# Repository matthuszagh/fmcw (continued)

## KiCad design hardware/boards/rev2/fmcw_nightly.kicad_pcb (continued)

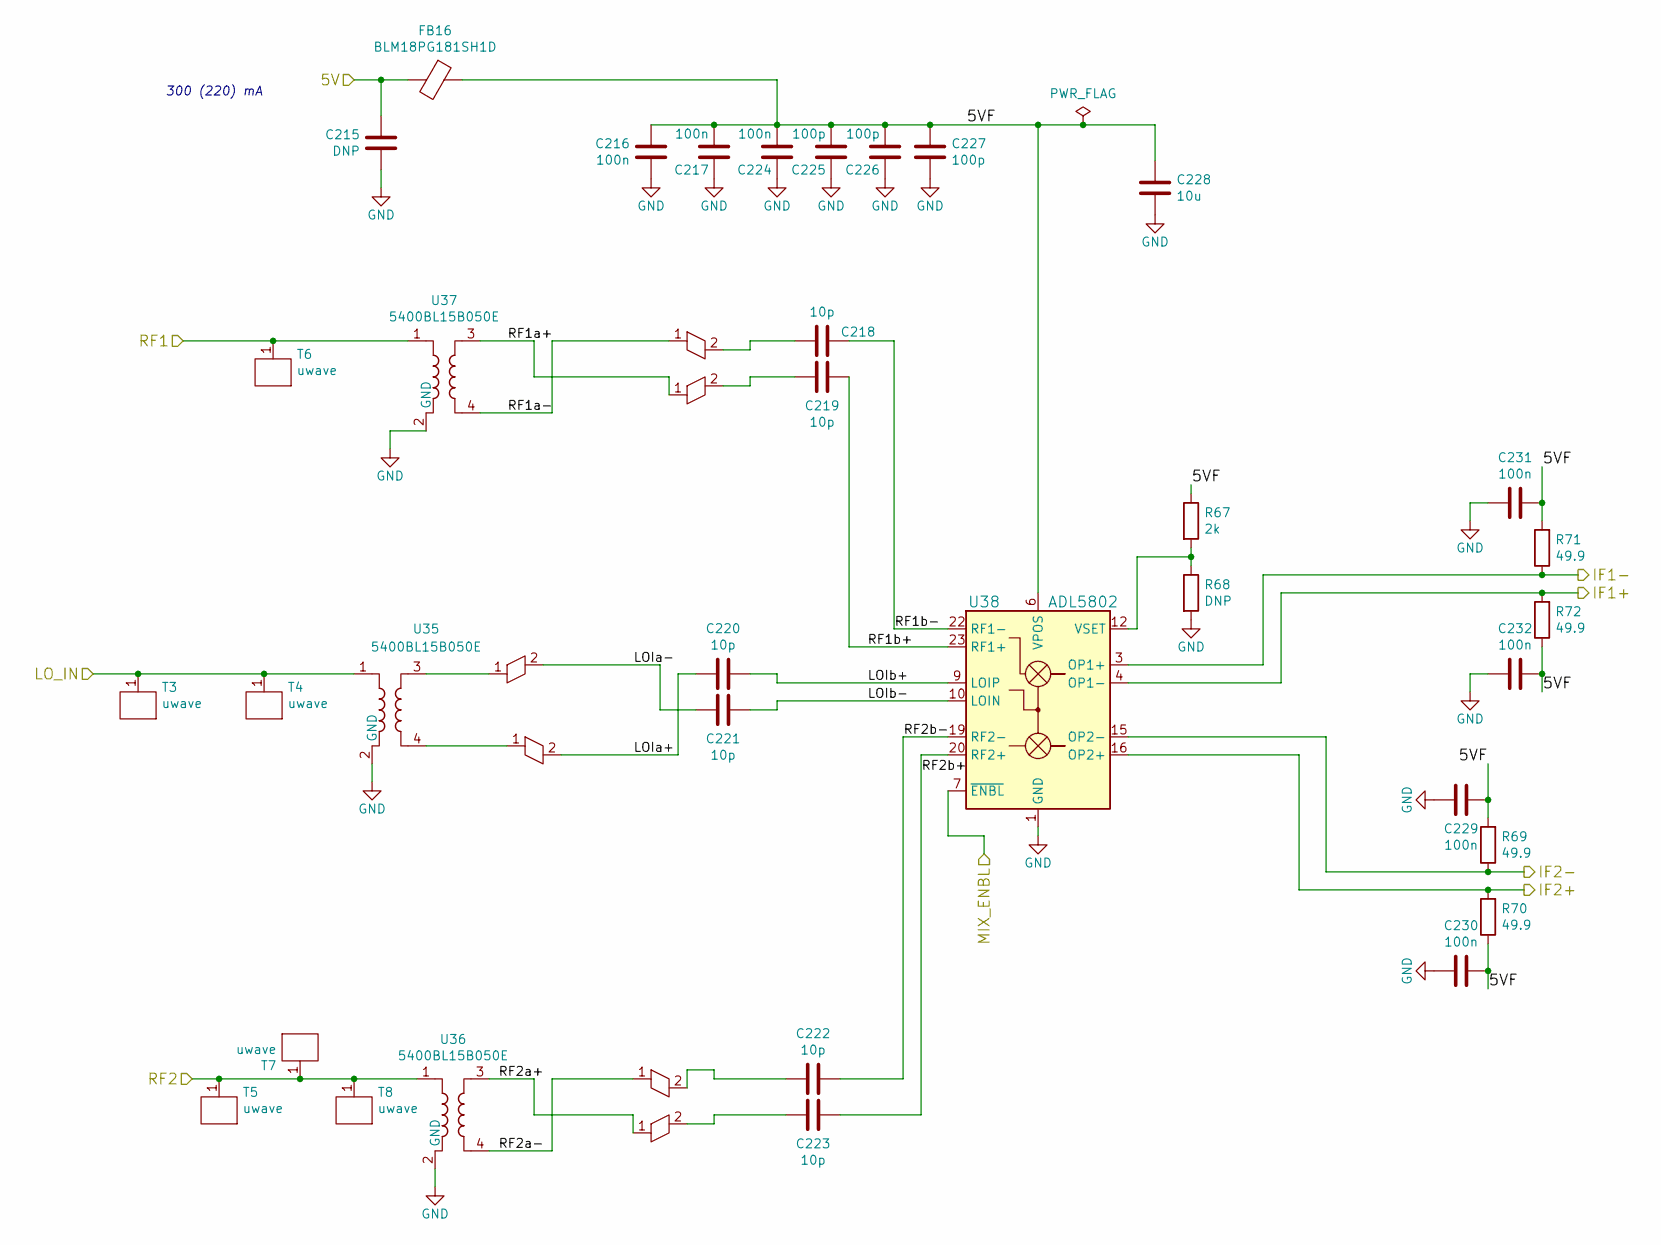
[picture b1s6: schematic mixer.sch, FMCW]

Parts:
C215: DNP; C_0805_2012Metric
C216, C217, C224, C229, C230, C231, C232: 100n; C_0402_1005Metric
C218, C219, C220, C221, C222, C223: 10p; RF_C_0201_0603Metric
C225, C226, C227: 100p; C_0402_1005Metric
C228: 10u; C_0805_2012Metric
FB16: BLM18PG181SH1D; L_0603_1608Metric
JP2, JP4, JP17: balun_exit_inv
JP3, JP5, JP18: balun_exit
R67: 2k; R_0402_1005Metric
R68: DNP; R_0402_1005Metric
R69, R70, R71, R72: 49.9; R_0402_1005Metric
T3, T4, T5, T6, T7, T8: uwave; uwm_0.38_0.17_90
U35, U36, U37: 5400BL15B050E; Balun_Johanson_5400BL15B050E
U38: ADL5802; LFCSP-24-1EP_4x4mm_P0.5mm_EP2.5x2.5mm_ThermalVias

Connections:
/5VMIX: C215.2, FB16.2; also elsewhere on the board
/IF1+: R72.2, U38.4 (OP1-); also elsewhere on the board
/IF1-: R71.1, U38.3 (OP1+); also elsewhere on the board
/IF2+: R70.2, U38.16 (OP2+); also elsewhere on the board
/IF2-: R69.1, U38.15 (OP2-); also elsewhere on the board
/LO: T3.1, T4.1, U35.1; also elsewhere on the board
/MIX_ENBL: U38.7 (~ENBL); also elsewhere on the board
/RF1: T6.1, U37.1; also elsewhere on the board
/RF2: T5.1, T7.1, T8.1, U36.1; also elsewhere on the board
/mixer/5VF: C216.2, C217.2, C224.2, C225.2, C226.2, C227.2, C228.2, C229.2, C230.2, C231.2, C232.2, FB16.1, R67.1, R69.2, R70.1, R71.2, R72.1, U38.6 (VPOS), U38.13 (VPOS), U38.24 (VPOS)
/mixer/LOIa+: C220.2, JP18.2
/mixer/LOIa-: C221.2, JP17.2
/mixer/LOIb+: C220.1, U38.9 (LOIP)
/mixer/LOIb-: C221.1, U38.10 (LOIN)
/mixer/RF1a+: JP4.1, U37.3
/mixer/RF1a-: JP5.1, U37.4
/mixer/RF1b+: C219.1, U38.23 (RF1+)
/mixer/RF1b-: C218.1, U38.22 (RF1-)
/mixer/RF2a+: JP2.1, U36.3
/mixer/RF2a-: JP3.1, U36.4
/mixer/RF2b+: C223.1, U38.20 (RF2+)
/mixer/RF2b-: C222.1, U38.19 (RF2-)
GND: C215.1, C216.1, C217.1, C224.1, C225.1, C226.1, C227.1, C228.1, C229.1, C230.1, C231.1, C232.1, R68.2, U35.2 (GND), U35.5 (GND), U36.2 (GND), U36.5 (GND), U37.2 (GND), U37.5 (GND), U38.1 (GND), U38.2 (GND), U38.5 (GND), U38.8 (GND), U38.11 (GND), U38.14 (GND), U38.17 (GND), U38.18 (GND), U38.21 (GND), U38.25 (GND); also elsewhere on the board
unnamed: C218.2, JP5.2
unnamed: C219.2, JP4.2
unnamed: C222.2, JP3.2
unnamed: C223.2, JP2.2
unnamed: JP17.1, U35.3
unnamed: JP18.1, U35.4
unnamed: R67.2, R68.1, U38.12 (VSET)

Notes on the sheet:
300 (220) mA

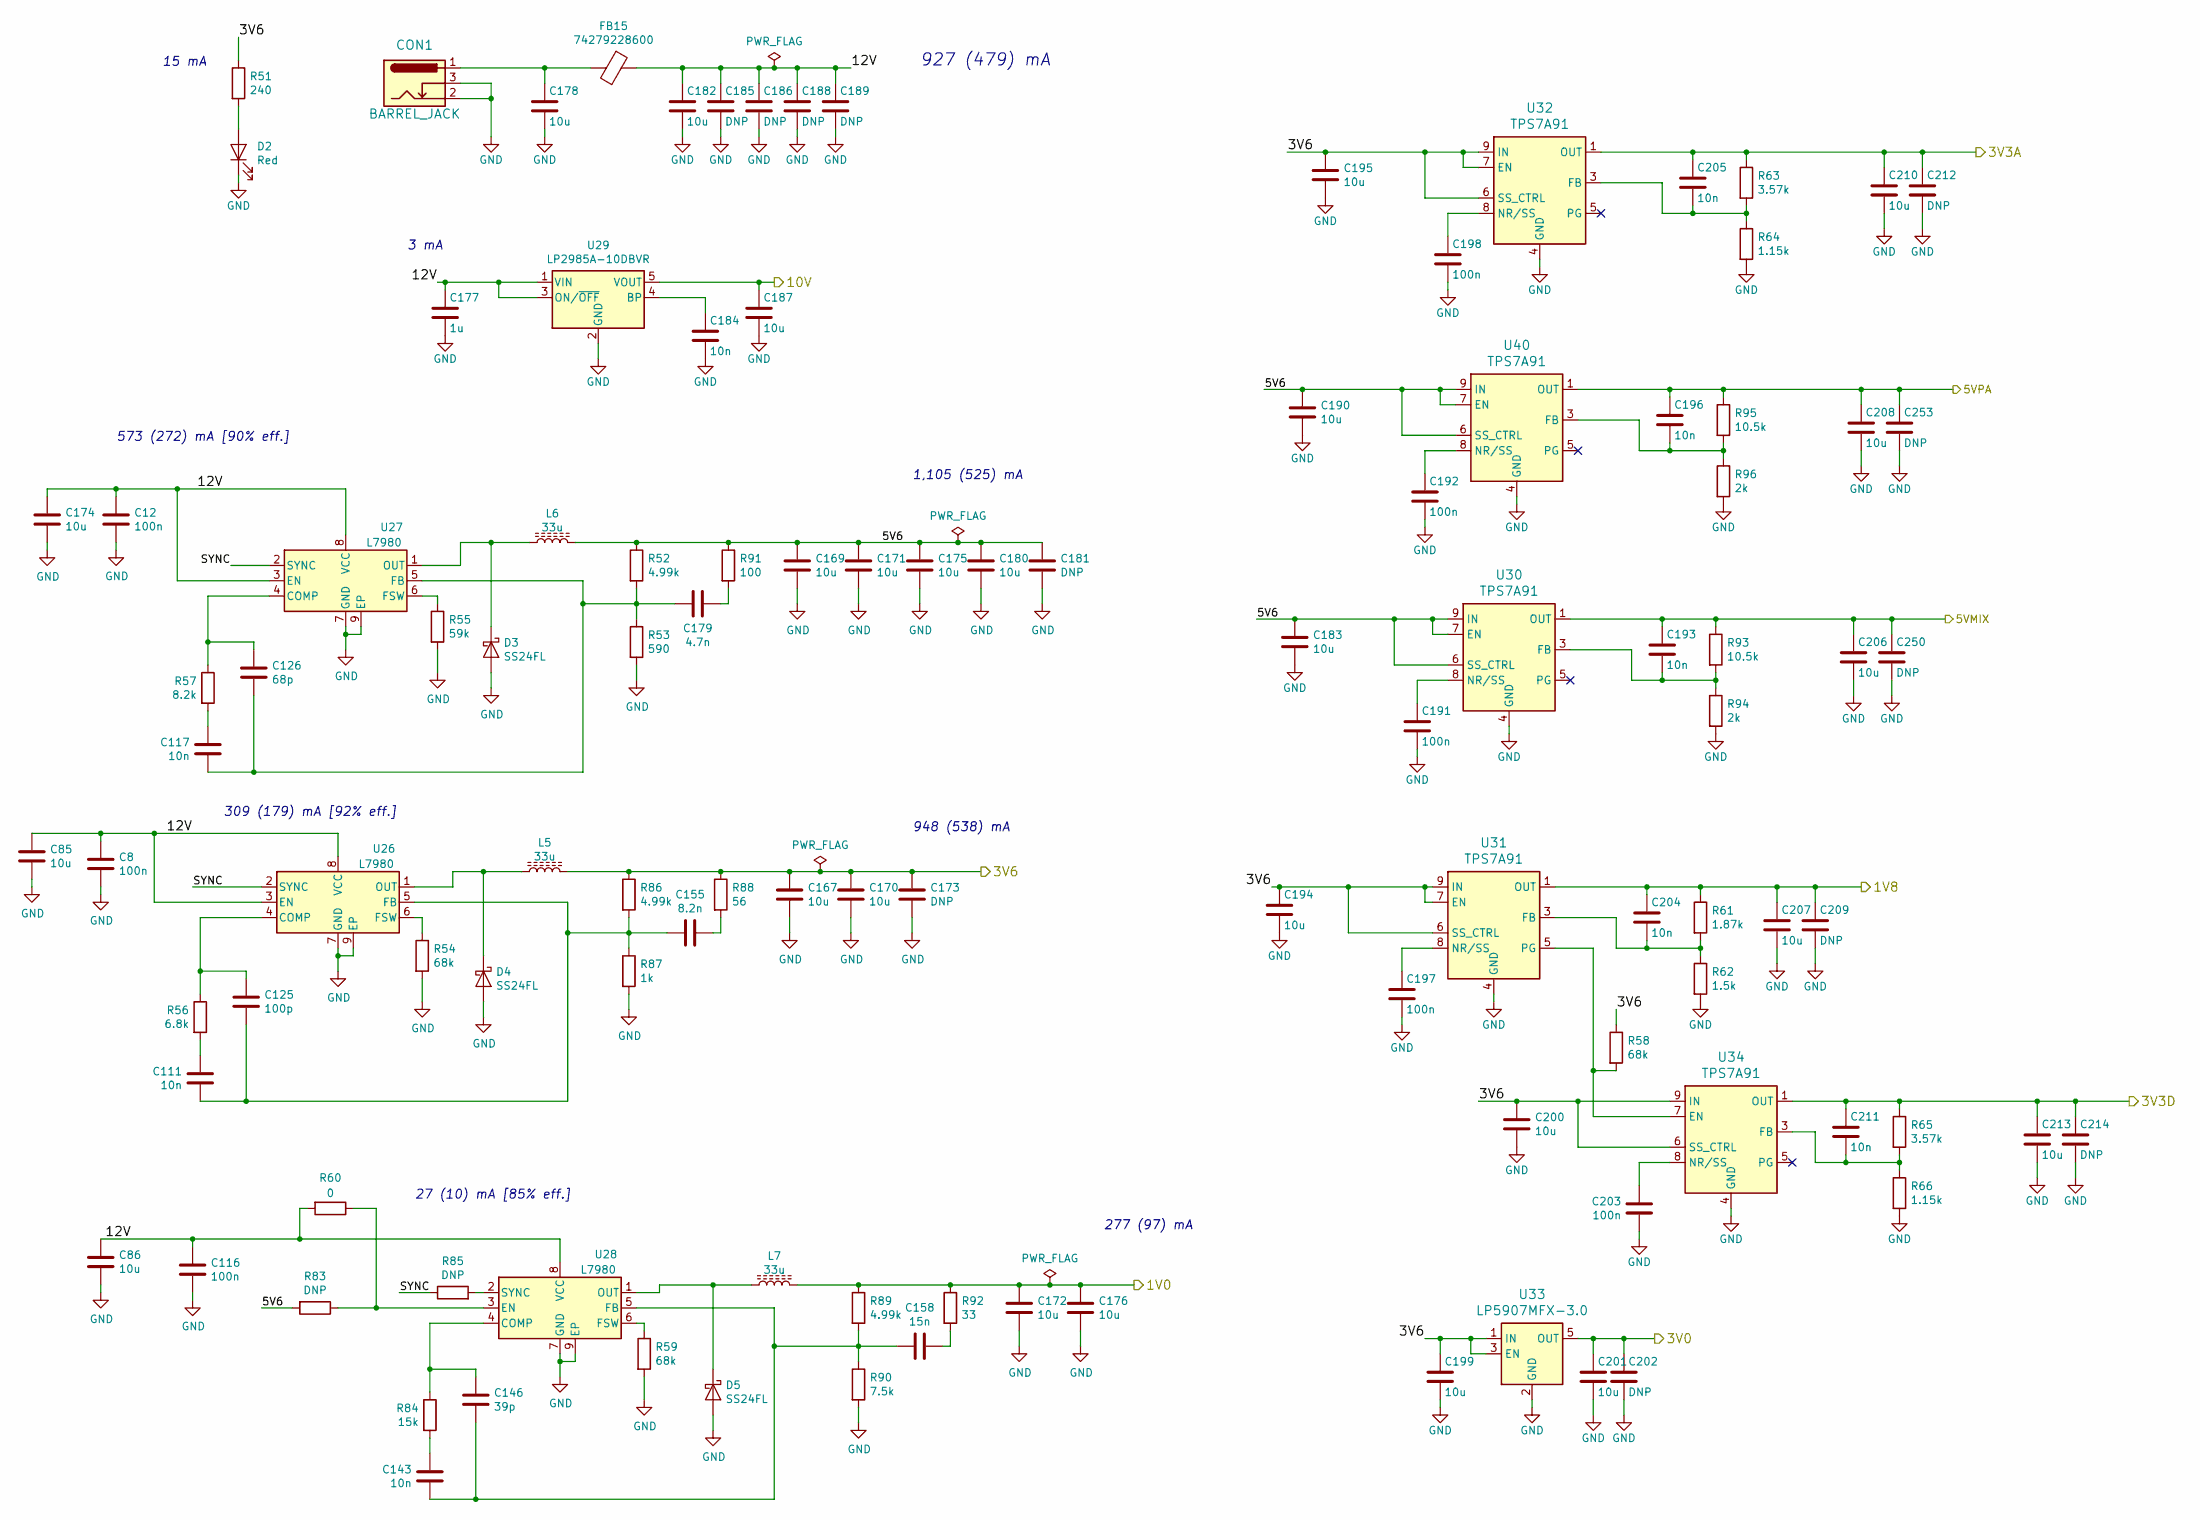
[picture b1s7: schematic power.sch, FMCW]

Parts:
C8, C12, C116, C191, C192, C197, C198, C203: 100n; C_0402_1005Metric
C85, C86, C167, C169, C170, C171, C172, C174, C175, C176, C178, C180, C182, C183, C187, C190, C194, C195, C199, C200, C201, C206, C207, C208, C210, C213: 10u; C_0805_2012Metric
C111, C117, C143, C184, C193, C196, C204, C205, C211: 10n; C_0402_1005Metric
C125: 100p; C_0402_1005Metric
C126: 68p; C_0402_1005Metric
C146: 39p; C_0402_1005Metric
C155: 8.2n; C_0402_1005Metric
C158: 15n; C_0402_1005Metric
C173, C181, C185, C186, C188, C189, C202, C209, C212, C214, C250, C253: DNP; C_0805_2012Metric
C177: 1u; C_0603_1608Metric
C179: 4.7n; C_0402_1005Metric
CON1: BARREL_JACK; BarrelJack_Wuerth_6941xx301002
D2: Red; LED_0603_1608Metric
D3, D4, D5: SS24FL; D_SOD-123F
FB15: 74279228600; L_0603_1608Metric
L5, L6: 33u; L_Wuerth_HCI-1365
L7: 33u; SRR6040A
R51: 240; R_0402_1005Metric
R52, R86, R89: 4.99k; R_0402_1005Metric
R53: 590; R_0402_1005Metric
R54, R58, R59: 68k; R_0402_1005Metric
R55: 59k; R_0402_1005Metric
R56: 6.8k; R_0402_1005Metric
R57: 8.2k; R_0402_1005Metric
R60: 0; R_0402_1005Metric
R61: 1.87k; R_0402_1005Metric
R62: 1.5k; R_0402_1005Metric
R63, R65: 3.57k; R_0402_1005Metric
R64, R66: 1.15k; R_0402_1005Metric
R83, R85: DNP; R_0402_1005Metric
R84: 15k; R_0402_1005Metric
R87: 1k; R_0402_1005Metric
R88: 56; R_0402_1005Metric
R90: 7.5k; R_0402_1005Metric
R91: 100; R_0402_1005Metric
R92: 33; R_0402_1005Metric
R93, R95: 10.5k; R_0402_1005Metric
R94, R96: 2k; R_0402_1005Metric
U26, U27, U28: L7980; HSOP-8-1EP_3.9x4.9mm_P1.27mm_EP2.3x2.3mm_ThermalVias
U29: LP2985A-10DBVR; SOT-23-5
U30, U31, U32, U34, U40: TPS7A91; Texas_S-PDSO-N10_EP1.2x2mm
U33: LP5907MFX-3.0; SOT-23-5

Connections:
/1V0: C172.1, C176.1, L7.2, R89.1, R92.1; also elsewhere on the board
/1V8: C204.1, C207.1, C209.1, R61.1, U31.1 (OUT), U31.2 (OUT); also elsewhere on the board
/3V0: C201.1, C202.1, U33.5 (OUT); also elsewhere on the board
/3V3A: C205.1, C210.1, C212.1, R63.1, U32.1 (OUT), U32.2 (OUT); also elsewhere on the board
/3V6: C167.1, C170.1, C173.1, C194.1, C195.1, C199.1, C200.1, L5.2, R51.1, R58.1, R86.1, R88.1, U31.6 (SS_CTRL), U31.7 (EN), U31.9 (IN), U31.10 (IN), U32.6 (SS_CTRL), U32.7 (EN), U32.9 (IN), U32.10 (IN), U33.1 (IN), U33.3 (EN), U34.6 (SS_CTRL), U34.9 (IN), U34.10 (IN); also elsewhere on the board
/5VMIX: C193.1, C206.1, C250.1, R93.1, U30.1 (OUT), U30.2 (OUT); also elsewhere on the board
/5VPA: C196.1, C208.1, C253.1, R95.1, U40.1 (OUT), U40.2 (OUT); also elsewhere on the board
/10V: C187.1, U29.5 (VOUT); also elsewhere on the board
/power/5V6: C169.1, C171.1, C175.1, C180.1, C181.1, C183.1, C190.1, L6.2, R52.1, R83.2, R91.1, U30.6 (SS_CTRL), U30.7 (EN), U30.9 (IN), U30.10 (IN), U40.6 (SS_CTRL), U40.7 (EN), U40.9 (IN), U40.10 (IN)
/power/12V: C8.1, C12.1, C85.1, C86.1, C116.1, C174.1, C177.1, C182.1, C185.1, C186.1, C188.1, C189.1, FB15.1, R60.2, U26.3 (EN), U26.8 (VCC), U27.3 (EN), U27.8 (VCC), U28.8 (VCC), U29.1 (VIN), U29.3 (ON/~OFF~)
/power/SYNC: R85.1, U26.2 (SYNC), U27.2 (SYNC)
GND: C8.2, C12.2, C85.2, C86.2, C116.2, C167.2, C169.2, C170.2, C171.2, C172.2, C173.2, C174.2, C175.2, C176.2, C177.2, C178.2, C180.2, C181.2, C182.2, C183.2, C184.2, C185.2, C186.2, C187.2, C188.2, C189.2, C190.2, C191.2, C192.2, C194.2, C195.2, C197.2, C198.2, C199.2, C200.2, C201.2, C202.2, C203.2, C206.2, C207.2, C208.2, C209.2, C210.2, C212.2, C213.2, C214.2, C250.2, C253.2, CON1.2, CON1.3, D2.1 (K), D3.2 (A), D4.2 (A), D5.2 (A), R53.2, R54.2, R55.2, R59.2, R62.2, R64.2, R66.2, R87.2, R90.2, R94.2, R96.2, U26.7 (GND), U26.9 (EP), U27.7 (GND), U27.9 (EP), U28.7 (GND), U28.9 (EP), U29.2 (GND), U30.4 (GND), U30.11 (GND), U31.4 (GND), U31.11 (GND), U32.4 (GND), U32.11 (GND), U33.2 (GND), U34.4 (GND), U34.11 (GND), U40.4 (GND), U40.11 (GND); also elsewhere on the board
unnamed: C111.1, R56.2
unnamed: C111.2, C125.2, C155.2, R86.2, R87.1, U26.5 (FB)
unnamed: C117.1, R57.2
unnamed: C117.2, C126.2, C179.2, R52.2, R53.1, U27.5 (FB)
unnamed: C125.1, R56.1, U26.4 (COMP)
unnamed: C126.1, R57.1, U27.4 (COMP)
unnamed: C143.1, R84.2
unnamed: C143.2, C146.2, C158.2, R89.2, R90.1, U28.5 (FB)
unnamed: C146.1, R84.1, U28.4 (COMP)
unnamed: C155.1, R88.2
unnamed: C158.1, R92.2
unnamed: C178.1, CON1.1, FB15.2
unnamed: C179.1, R91.2
unnamed: C184.1, U29.4 (BP)
unnamed: C191.1, U30.8 (NR/SS)
unnamed: C192.1, U40.8 (NR/SS)
unnamed: C193.2, R93.2, R94.1, U30.3 (FB)
unnamed: C196.2, R95.2, R96.1, U40.3 (FB)
unnamed: C197.1, U31.8 (NR/SS)
unnamed: C198.1, U32.8 (NR/SS)
unnamed: C203.1, U34.8 (NR/SS)
unnamed: C204.2, R61.2, R62.1, U31.3 (FB)
unnamed: C205.2, R63.2, R64.1, U32.3 (FB)
unnamed: C211.2, R65.2, R66.1, U34.3 (FB)
unnamed: D2.2 (A), R51.2
unnamed: D3.1 (K), L6.1, U27.1 (OUT)
unnamed: D4.1 (K), L5.1, U26.1 (OUT)
unnamed: D5.1 (K), L7.1, U28.1 (OUT)
unnamed: R54.1, U26.6 (FSW)
unnamed: R55.1, U27.6 (FSW)
unnamed: R58.2, U31.5 (PG), U34.7 (EN)
unnamed: R59.1, U28.6 (FSW)
unnamed: R60.1, R83.1, U28.3 (EN)
unnamed: R85.2, U28.2 (SYNC)

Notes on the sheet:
573 (272) mA [90% eff.]
15 mA
309 (179) mA [92% eff.]
3 mA
27 (10) mA [85% eff.]
1,105 (525) mA
948 (538) mA
927 (479) mA
277 (97) mA

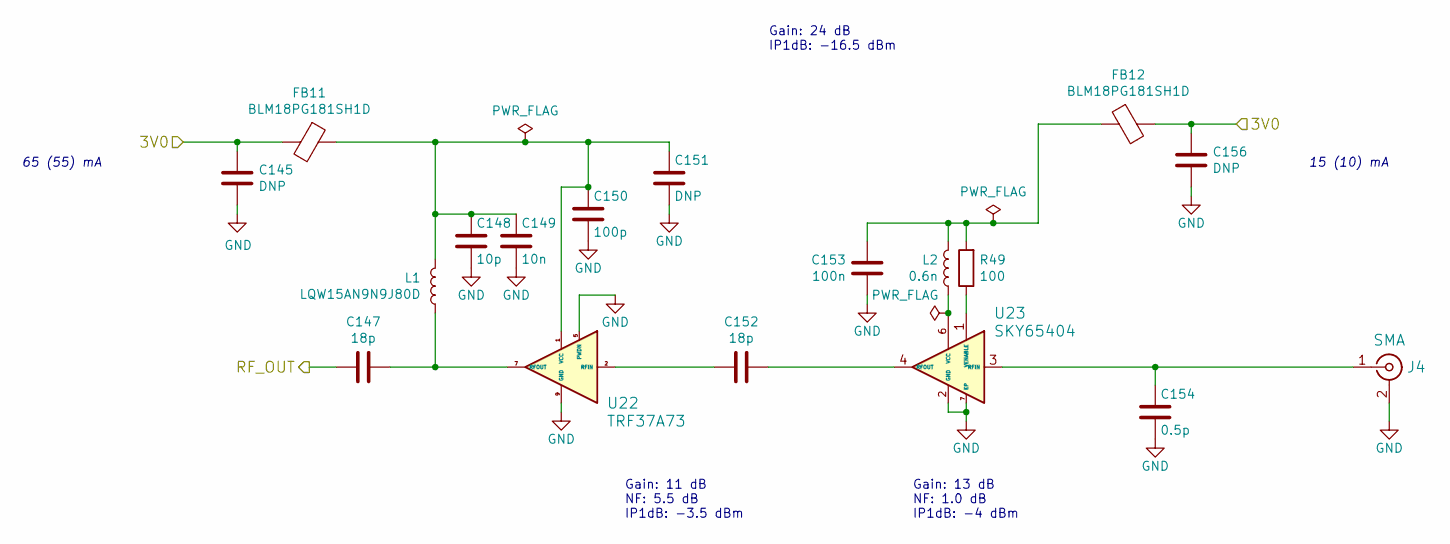
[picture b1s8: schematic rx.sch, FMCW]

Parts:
C145, C156: DNP; C_0805_2012Metric
C147, C152: 18p; RF_C_0201_0603Metric
C148: 10p; C_0402_1005Metric
C149: 10n; C_0402_1005Metric
C150: 100p; C_0402_1005Metric
C153: 100n; C_0402_1005Metric
C154: 0.5p; RF_C_0201_0603Metric
C163: DNP; C_0603_1608Metric
FB13, FB14: BLM18PG181SH1D; L_0603_1608Metric
J4: SMA; SMA_901-10512
L1: LQW15AN9N9J80D; RF_Bypass_C_0402_1005Metric
L2: 0.6n; L_0402_1005Metric
R49: 100; R_0402_1005Metric
U22: TRF37A73; WSON-8-1EP_2x2mm_P0.5mm_EP0.9x1.6mm_ThermalVias
U23: SKY65404; Skyworks_SKY65404-31

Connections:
/3V0: C145.1, C156.1, FB13.2, FB14.2; also elsewhere on the board
/RF1: C147.2; also elsewhere on the board
GND: C145.2, C148.2, C149.2, C150.2, C153.2, C154.2, C156.2, C163.2, J4.2 (Ext), U22.5 (PWDN), U22.9 (GND), U23.2 (GND), U23.5 (GND), U23.7 (EP); also elsewhere on the board
unnamed: C147.1, L1.1, U22.7 (RFOUT)
unnamed: C152.1, U23.4 (RFOUT)
unnamed: C152.2, U22.2 (RFIN)
unnamed: C154.1, J4.1 (In), U23.3 (RFIN)
unnamed: L2.1, U23.6 (VCC)
unnamed: R49.1, U23.1 (VENABLE)

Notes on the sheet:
65 (55) mA
Gain: 11 dB NF: 5.5 dB IP1dB: -3.5 dBm
Gain: 24 dB IP1dB: -16.5 dBm
Gain: 13 dB NF: 1.0 dB IP1dB: -4 dBm
15 (10) mA

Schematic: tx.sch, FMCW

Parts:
C4, C118: 10u; C_0805_2012Metric
C6, C124: 220p; C_0402_1005Metric
C102, C104, C105, C108, C115, C121, C127, C131, C135: 100n; C_0402_1005Metric
C103, C106, C107, C109: 10p; C_0402_1005Metric
C110: 2.2n; C_0402_1005Metric
C112, C251, C252: 10p; RF_C_0201_0603Metric
C113: DNP; C_0805_2012Metric
C114: 51p; C_0402_1005Metric
C119: 10n; C_0402_1005Metric
C120: 68p; C_0402_1005Metric
C267: 0.3p; RF_C_0201_0603Metric
FB6, FB7: BLM18PG181SH1D; L_0603_1608Metric
FB8: CIC21P101NE; L_0805_2012Metric
J3: SMA; SMA_901-10512
L12: 4.7n; L_0402_1005Metric
Q2: RE1C002UN; SOT-416
R37: 5.49k; R_0402_1005Metric
R38, R44: DNP; R_0402_1005Metric
R39: 3.09k; R_0402_1005Metric
R40, R41, R42: 4.7k; R_0402_1005Metric
R43: 47k; R_0402_1005Metric
R45: 1.5k; R_0402_1005Metric
R46: 10k; R_0402_1005Metric
R47: 100; R_0603b
R48: 49.9; R_0402_1005Metric
R97: 1.3k; R_0402_1005Metric
R114: 510; R_0402_1005Metric
R115: 3.3; R_0402_1005Metric
T1, T2: uwave; uwm_0.38_0.17_90
U12: ADF4158; LFCSP-24-1EP_4x4mm_P0.5mm_EP2.5x2.5mm_ThermalVias
U13: TLV172DCK; SOT-353_SC-70-5
U14: PAT1220-C-3DB; RF_Attenuator_Susumu_PAT1220
U15: HMC431; QFN-24-1EP_4x4mm_P0.5mm_EP2.8x2.8mm_ThermalVias
U16: PD4859J5050S2HF; Anaren_0805_2012Metric-6
U17: PAT1220-C-5DB; RF_Attenuator_Susumu_PAT1220
U18: SE5004L; Skyworks_SE5004L
U20: PAT1220-C-6DB; RF_Attenuator_Susumu_PAT1220
U21: LMV321; SOT-23-5
Z1: BRANCHLINE-fmcw3-rescue; coupler_20db

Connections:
/3V0: FB7.2; also elsewhere on the board
/3V3A: C102.1, C103.1, C104.1, C105.1, C106.1, C121.2, R43.1, R45.1, U12.6 (AVDD), U12.7 (AVDD), U12.8 (AVDD), U12.18 (SDVDD), U12.19 (DVDD), U21.5 (V+); also elsewhere on the board
/5VPA: C113.1, FB6.2, FB8.2; also elsewhere on the board
/10V: C115.2, U13.5 (V+); also elsewhere on the board
/ADF_CE: U12.13 (CE); also elsewhere on the board
/ADF_CLK: U12.14 (CLK); also elsewhere on the board
/ADF_DATA: U12.15 (DATA); also elsewhere on the board
/ADF_LE: U12.16 (LE); also elsewhere on the board
/ADF_MUXOUT: U12.17 (MUXOUT); also elsewhere on the board
/ADF_REF: U12.9 (REFIN); also elsewhere on the board
/ADF_TXDATA: U12.12 (TXDATA); also elsewhere on the board
/LO: U20.1; also elsewhere on the board
/PA_OFF: Q2.1 (G), R43.2, R44.1; also elsewhere on the board
/tx/5V_PA: C4.2, C6.2, C131.1, C135.2, FB8.1, U18.8 (VCC2), U18.9 (VCC3), U18.18 (VCC3), U18.19 (VCC2), U18.20 (VCC1)
/tx/5V_SYNTH: C108.1, C109.1, FB6.1, U12.22 (VP)
GND: C4.1, C102.2, C103.2, C104.2, C105.2, C106.2, C107.1, C108.2, C109.2, C113.2, C114.2, C115.1, C118.1, C119.1, C120.2, C121.1, C131.2, C135.1, C267.1, J3.2 (Ext), Q2.2 (S), R37.2, R39.1, R40.2, R44.2, R46.2, R48.1, R115.1, U12.1 (CPGND), U12.2 (AGND), U12.3 (AGND), U12.10 (DGND), U12.11 (SDGND), U12.25 (AGND), U13.2 (V-), U14.3, U15.1 (NC), U15.2 (NC), U15.3 (NC), U15.4 (NC), U15.5 (NC), U15.6 (NC), U15.7 (NC), U15.8 (NC), U15.9 (NC), U15.10 (NC), U15.11 (NC), U15.12 (NC), U15.13 (NC), U15.14 (NC), U15.15 (GND), U15.17 (NC), U15.18 (NC), U15.19 (NC), U15.21 (NC), U15.23 (NC), U15.24 (NC), U15.25 (GND), U16.1 (GND), U16.3 (GND), U16.5 (GND), U17.3, U18.1 (GND), U20.3, U21.2 (V-); also elsewhere on the board
unnamed: C6.1, R115.2
unnamed: C107.2, U12.4 (RFINB)
unnamed: C110.1, C114.1, U12.24 (CP), U13.1 (+)
unnamed: C110.2, R38.1, R39.2
unnamed: C112.1, U14.1
unnamed: C112.2, U12.5 (RFINA)
unnamed: C118.2, C119.2, FB7.1, U15.20 (VCC)
unnamed: C120.1, R42.1, U15.22 (VTUNE)
unnamed: C124.1, U18.7 (SP2)
unnamed: C124.2, L12.2
unnamed: C127.1, R114.2
unnamed: C127.2, L12.1, R97.1, U18.5 (VREF), U21.4
unnamed: C251.1, U18.3 (RFIN)
unnamed: C251.2, U17.2
unnamed: C252.1, C267.2, Z1.1
unnamed: C252.2, U18.13 (RFOUT)
unnamed: J3.1 (In), Z1.2
unnamed: Q2.3 (D), R45.2, R46.1, U21.1 (+)
unnamed: R37.1, U12.23 (RSET)
unnamed: R38.2, U12.20 (SW1)
unnamed: R40.1, R41.2, U13.3 (-)
unnamed: R41.1, R42.2, U13.4
unnamed: R47.1, U16.4 (Output1), U17.1
unnamed: R47.2, T1.1, T2.1, U14.2, U16.6 (Output2)
unnamed: R48.2, Z1.4
unnamed: R97.2, U21.3 (-)
unnamed: R114.1, U18.6 (SP1)
unnamed: U15.16 (RFOUT), U16.2 (Input)
unnamed: U20.2, Z1.3

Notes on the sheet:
32 (23) mA
-4 dBm
5 mA
3 mA
27mA
10 mA
+2dBm
-1 dBm
2.85V
800 (300) mA
-6 dBm
26 dBm
6 dBm

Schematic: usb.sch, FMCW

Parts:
C59, C62, C63, C64, C65, C69, C70, C71, C72, C73, C74: 100n; C_0402_1005Metric
C60, C61: 15p; C_0402_1005Metric
C66, C67, C68: 4.7u; C_0603_1608Metric
FB3, FB4: BLM18PG181SH1D; L_0603_1608Metric
J2: USB_B_Micro; USB_Micro-B_Amphenol_10103594-0001LF_Horizontal
R3, R17, R27, R82: 10k; R_0402_1005Metric
R18: 2.2k; R_0402_1005Metric
R19: 12k; R_0402_1005Metric
R20, R21: 0; R_0402_1005Metric
R22: 1k; R_0402_1005Metric
R23, R24, R25: 33; R_0402_1005Metric
R26: 4.7k; R_0402_1005Metric
U8: 93LCxxBxxOT; SOT-23-6
U9: FT2232H; LQFP-64_10x10mm_P0.5mm
Y1: 12MHz; ABM10

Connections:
/fpga/CLKOUT: U9.32 (ACBUS5); also elsewhere on the board
/fpga/FT_D0: U9.16 (ADBUS0); also elsewhere on the board
/fpga/FT_D1: U9.17 (ADBUS1); also elsewhere on the board
/fpga/FT_D2: U9.18 (ADBUS2); also elsewhere on the board
/fpga/FT_D3: U9.19 (ADBUS3); also elsewhere on the board
/fpga/FT_D4: U9.21 (ADBUS4); also elsewhere on the board
/fpga/FT_D5: U9.22 (ADBUS5); also elsewhere on the board
/fpga/FT_D6: U9.23 (ADBUS6); also elsewhere on the board
/fpga/FT_D7: U9.24 (ADBUS7); also elsewhere on the board
/fpga/FT_SUSPEND: U9.36 (~SUSPEND); also elsewhere on the board
/fpga/OE#: U9.33 (ACBUS6); also elsewhere on the board
/fpga/RD#: U9.28 (ACBUS2); also elsewhere on the board
/fpga/RXF#: U9.26 (ACBUS0); also elsewhere on the board
/fpga/SIWUA: U9.30 (ACBUS4); also elsewhere on the board
/fpga/TCK: R23.1; also elsewhere on the board
/fpga/TDI: R25.1; also elsewhere on the board
/fpga/TDO: U9.40 (BDBUS2); also elsewhere on the board
/fpga/TMS: R24.1; also elsewhere on the board
/fpga/TXE#: U9.27 (ACBUS1); also elsewhere on the board
/fpga/WR: U9.29 (ACBUS3); also elsewhere on the board
/fpga/usb/1V8: C62.1, C63.1, C64.1, C67.1, U9.12 (VCORE), U9.37 (VCORE), U9.49 (VREGOUT), U9.64 (VCORE)
/fpga/usb/DO: R17.2, R18.1, U8.1 (DO)
/fpga/usb/EECLK: R3.2, U8.4 (CLK), U9.62 (EECLK)
/fpga/usb/EECS: R82.2, U8.5 (CS), U9.63 (EECS)
/fpga/usb/EEDATA: R18.2, U8.3 (DI), U9.61 (EEDATA)
/fpga/usb/USBD_N: R20.1, U9.7 (DM)
/fpga/usb/USBD_P: R21.1, U9.8 (DP)
/fpga/usb/USBDa_N: J2.2 (D-), R20.2
/fpga/usb/USBDa_P: J2.3 (D+), R21.2
/fpga/usb/USB_5V: J2.1 (VBUS), R26.1
GND: C59.2, C60.2, C61.2, C62.2, C63.2, C64.2, C65.1, C66.2, C67.2, C68.2, C69.2, C70.2, C71.2, C72.2, C73.2, C74.2, J2.5 (GND), J2.6 (Shield), R19.2, R27.2, U8.2 (GND), U9.1 (GND), U9.5 (GND), U9.10 (AGND), U9.11 (GND), U9.13 (TEST), U9.15 (GND), U9.25 (GND), U9.35 (GND), U9.47 (GND), U9.51 (GND); also elsewhere on the board
unnamed: C60.1, U9.2 (OSCI), Y1.1
unnamed: C61.1, U9.3 (OSCO), Y1.3
unnamed: C66.1, C69.1, FB4.2, U9.4 (VPHY)
unnamed: C68.1, C70.1, FB3.1, U9.9 (VPLL)
unnamed: R19.1, U9.6 (REF)
unnamed: R22.1, U9.14 (~RESET)
unnamed: R23.2, U9.38 (BDBUS0)
unnamed: R24.2, U9.41 (BDBUS3)
unnamed: R25.2, U9.39 (BDBUS1)
unnamed: R26.2, R27.1, U9.59 (BCBUS7)

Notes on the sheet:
70 mA
150 mA

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
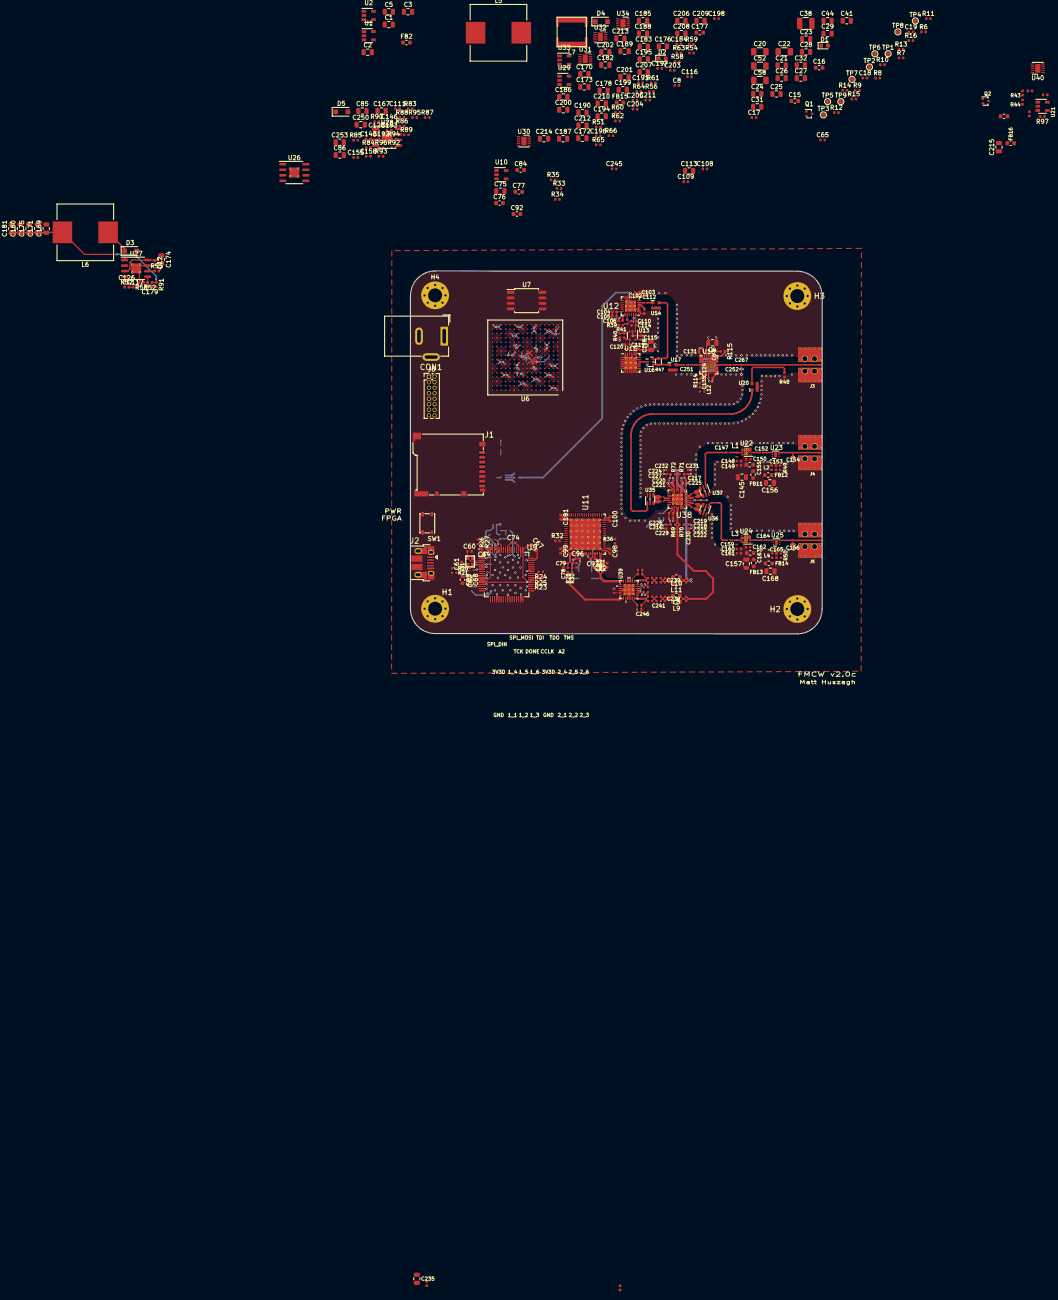
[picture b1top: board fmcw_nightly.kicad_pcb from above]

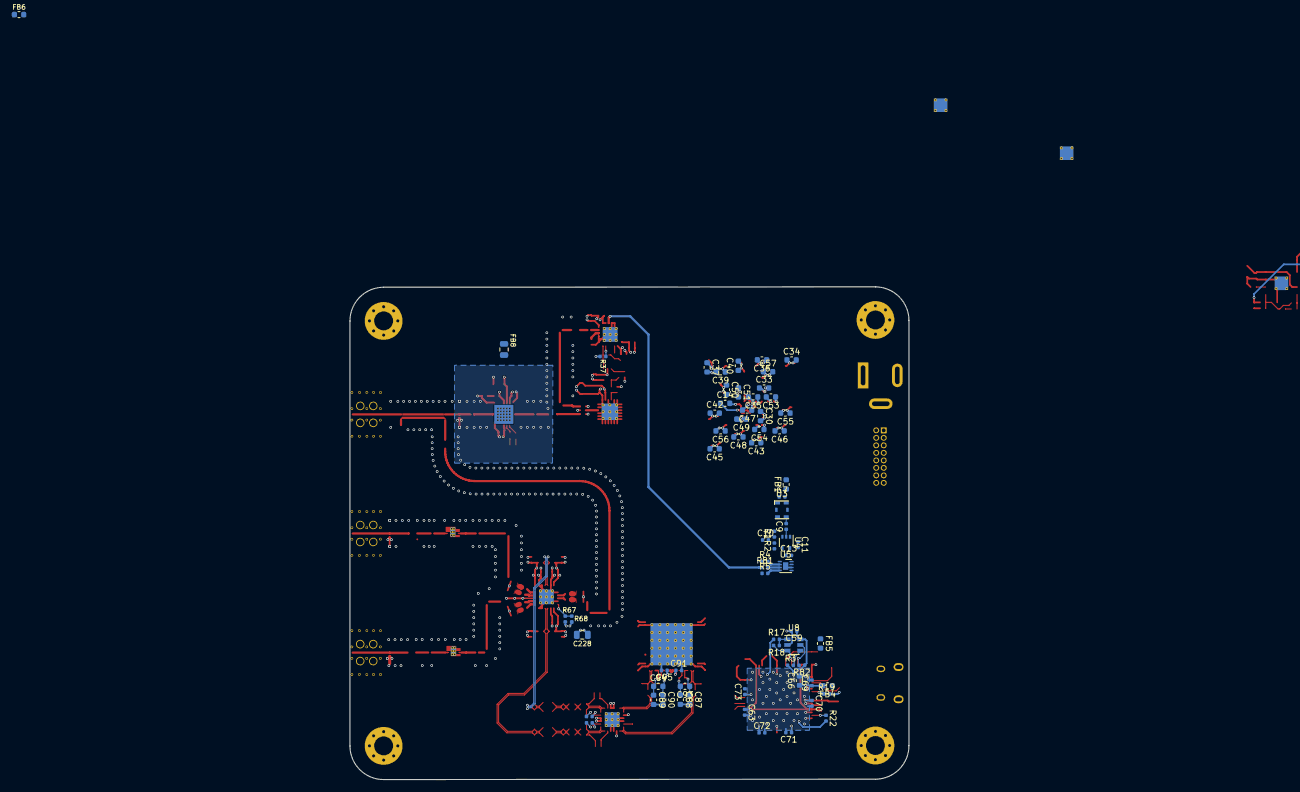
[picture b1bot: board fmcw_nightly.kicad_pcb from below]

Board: 4 copper layers, 94.6 x 83.4 mm, 446 parts (70 on the bottom side), 272 nets.

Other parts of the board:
C151: DNP; C_0603_1608Metric
C157, C168: DNP; C_0805_2012Metric
C159, C164: 18p; RF_C_0201_0603Metric
C160: 10p; C_0402_1005Metric
C161: 10n; C_0402_1005Metric
C162: 100p; C_0402_1005Metric
C165: 100n; C_0402_1005Metric
C166: 0.5p; RF_C_0201_0603Metric
FB5, FB11, FB12: BLM18PG181SH1D; L_0603_1608Metric
J5: SMA; SMA_901-10512
L3: LQW15AN9N9J80D; RF_Bypass_C_0402_1005Metric
L4: 0.6n; L_0402_1005Metric
R50: 100; R_0402_1005Metric
U24: TRF37A73; WSON-8-1EP_2x2mm_P0.5mm_EP0.9x1.6mm_ThermalVias
U25: SKY65404; Skyworks_SKY65404-31

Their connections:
/3V0: C157.1, C168.1, FB11.2, FB12.2; also elsewhere on the board
/RF2: C159.2; also elsewhere on the board
GND: C151.2, C157.2, C160.2, C161.2, C162.2, C165.2, C166.2, C168.2, J5.2 (Ext), U24.5 (PWDN), U24.9 (GND), U25.2 (GND), U25.5 (GND), U25.7 (EP); also elsewhere on the board
unnamed: C159.1, L3.1, U24.7 (RFOUT)
unnamed: C164.1, U25.4 (RFOUT)
unnamed: C164.2, U24.2 (RFIN)
unnamed: C166.1, J5.1 (In), U25.3 (RFIN)
unnamed: L4.1, U25.6 (VCC)
unnamed: R50.1, U25.1 (VENABLE)

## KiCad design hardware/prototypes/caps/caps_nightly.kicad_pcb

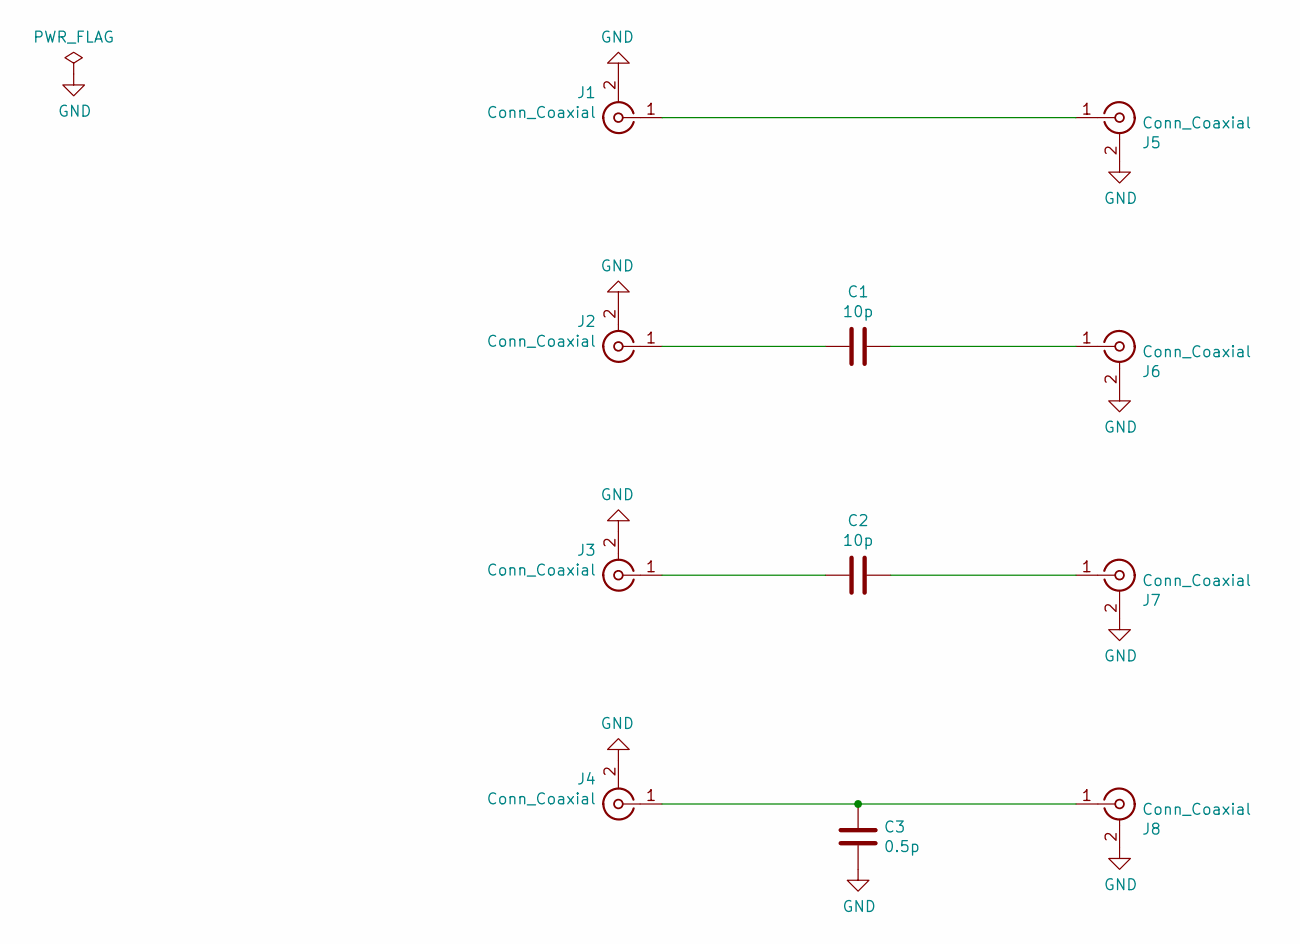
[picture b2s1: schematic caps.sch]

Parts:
C1: 10p; RF_C_0201_0603Metric
C2: 10p; RF_C_0402_1005Metric
C3: 0.5p; RF_C_0201_0603Metric
J1, J2, J3, J4, J5, J6, J7, J8: Conn_Coaxial; SMA_901-10512

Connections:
GND: C3.1, J1.2 (Ext), J2.2 (Ext), J3.2 (Ext), J4.2 (Ext), J5.2 (Ext), J6.2 (Ext), J7.2 (Ext), J8.2 (Ext)
unnamed: C1.1, J2.1 (In)
unnamed: C1.2, J6.1 (In)
unnamed: C2.1, J3.1 (In)
unnamed: C2.2, J7.1 (In)
unnamed: C3.2, J4.1 (In), J8.1 (In)
unnamed: J1.1 (In), J5.1 (In)

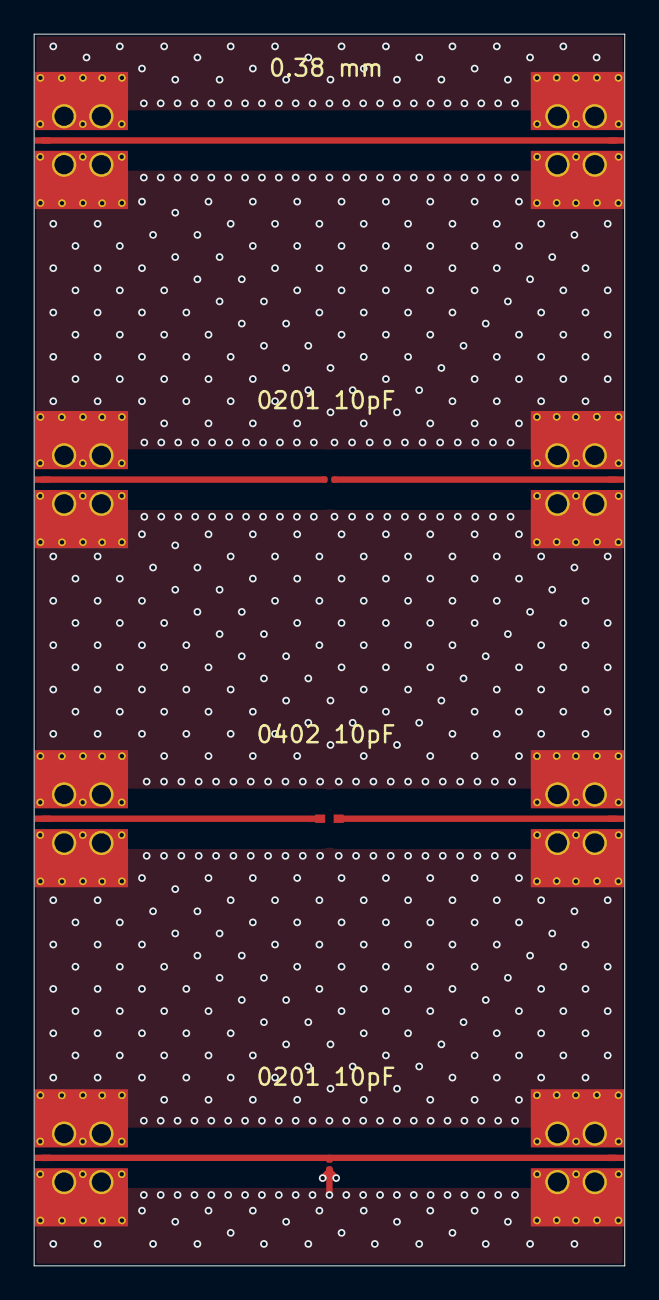
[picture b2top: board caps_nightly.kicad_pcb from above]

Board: 4 copper layers, 35.0 x 73.0 mm, 11 parts (0 on the bottom side), 7 nets.

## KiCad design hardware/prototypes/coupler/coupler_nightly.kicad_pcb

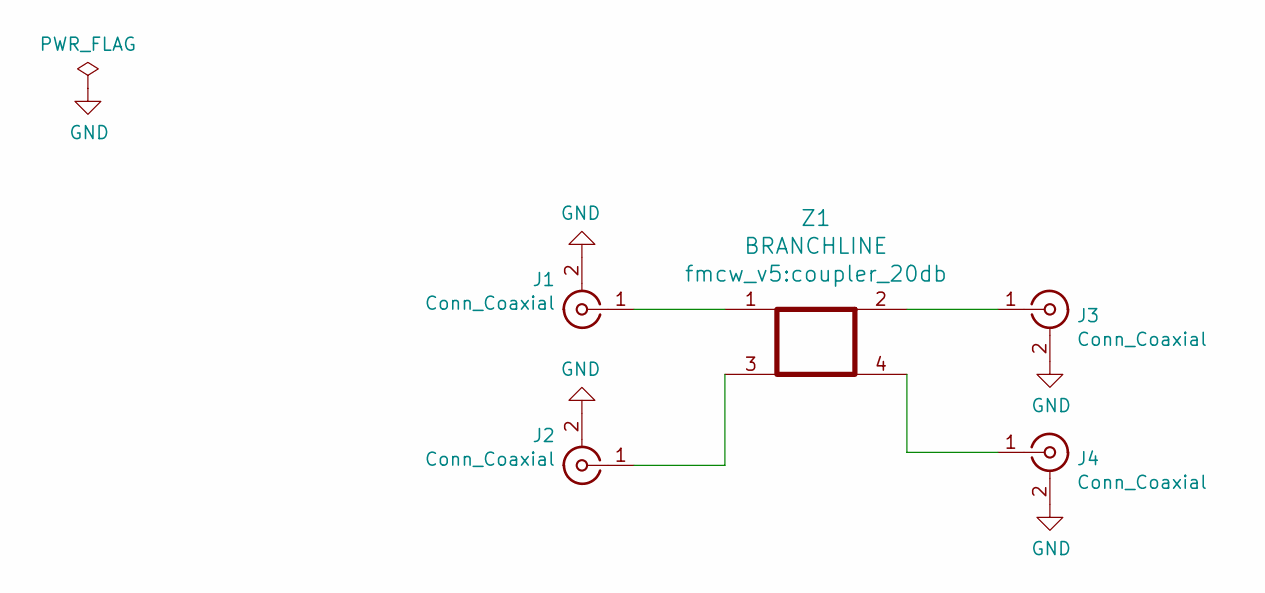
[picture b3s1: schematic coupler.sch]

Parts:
J1, J2, J3, J4: Conn_Coaxial; BU-1420701851_SMA
Z1: BRANCHLINE; coupler_20db

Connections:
GND: J1.2 (Ext), J2.2 (Ext), J3.2 (Ext), J4.2 (Ext)
unnamed: J1.1 (In), Z1.1
unnamed: J2.1 (In), Z1.3
unnamed: J3.1 (In), Z1.2
unnamed: J4.1 (In), Z1.4

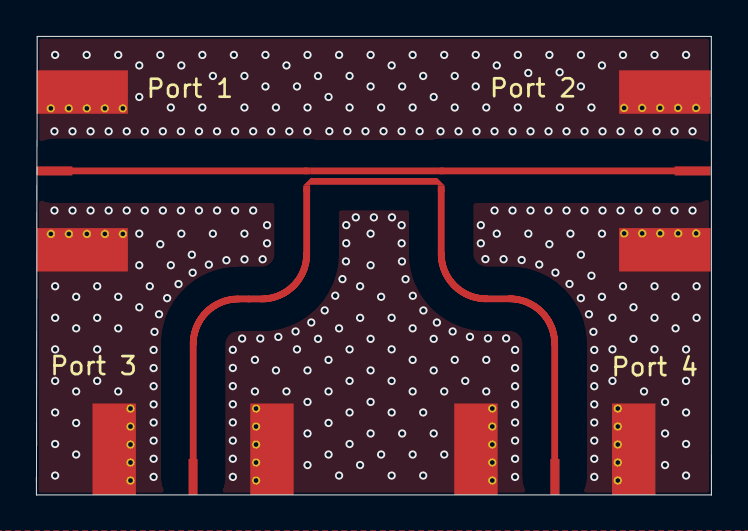
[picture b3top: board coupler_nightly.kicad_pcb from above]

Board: 4 copper layers, 37.5 x 25.5 mm, 5 parts (0 on the bottom side), 5 nets.
